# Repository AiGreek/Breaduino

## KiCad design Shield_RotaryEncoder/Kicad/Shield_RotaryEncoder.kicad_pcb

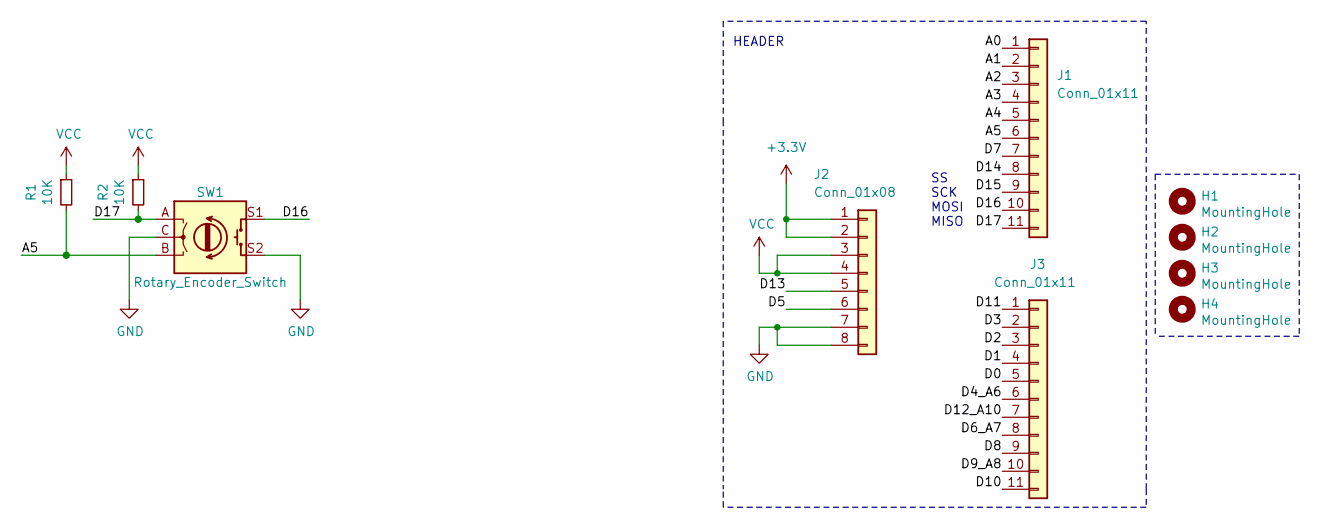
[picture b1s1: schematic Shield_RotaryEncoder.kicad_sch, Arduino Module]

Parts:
H1, H2, H3, H4: MountingHole; MountingHole_2.2mm_M2_Pad
J1, J3: Conn_01x11; PinHeader_1x11_P2.54mm_Vertical
J2: Conn_01x08; PinHeader_1x08_P2.54mm_Vertical
R1, R2: 10K; R_0603_1608Metric_Pad0.98x0.95mm_HandSolder
SW1: Rotary_Encoder_Switch; RotaryEncoder_Alps_EC11E-Switch_Vertical_H20mm

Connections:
+3V3: J2.1, J2.2
/A0: J1.1
/A1: J1.2
/A2: J1.3
/A3: J1.4
/A4: J1.5
/A5: J1.6, R1.2, SW1.B
/D0: J3.5
/D1: J3.4
/D2: J3.3
/D3: J3.2
/D4_A6: J3.6
/D5: J2.6
/D6_A7: J3.8
/D7: J1.7
/D8: J3.9
/D9_A8: J3.10
/D10: J3.11
/D11: J3.1
/D12_A10: J3.7
/D13: J2.5
/D14: J1.8
/D15: J1.9
/D16: J1.10, SW1.S1
/D17: J1.11, R2.2, SW1.A
GND: J2.7, J2.8, SW1.C, SW1.S2
VCC: J2.3, J2.4, R1.1, R2.1

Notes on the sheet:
HEADER
SS SCK MOSI MISO

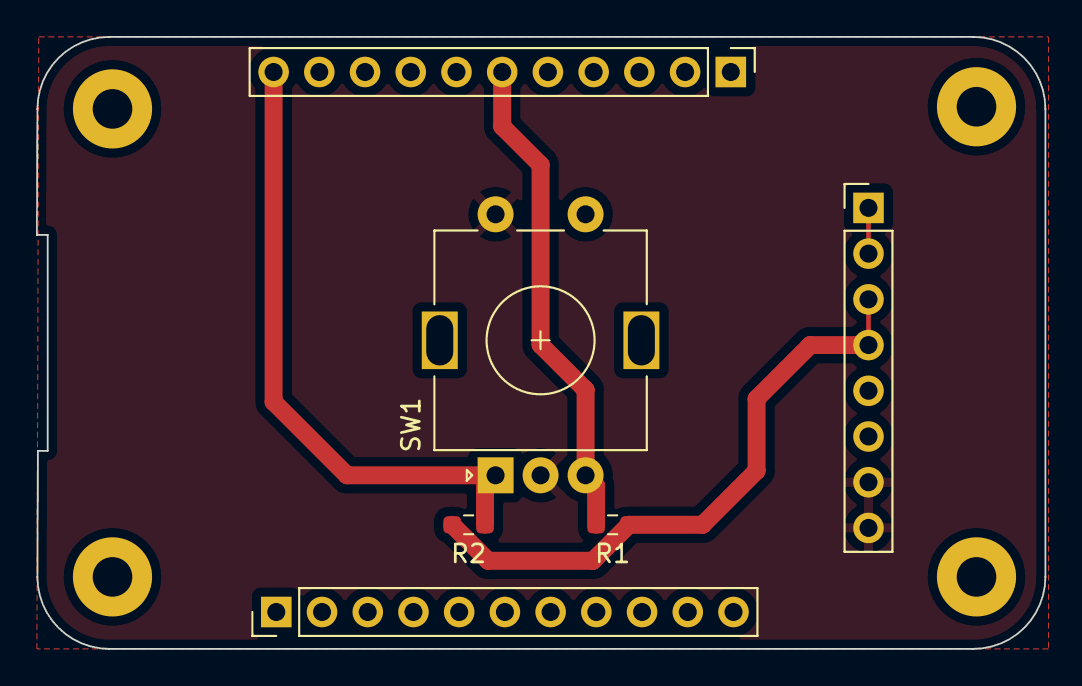
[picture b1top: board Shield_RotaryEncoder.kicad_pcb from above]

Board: 2 copper layers, 56.0 x 34.0 mm, 10 parts (0 on the bottom side), 6 nets.

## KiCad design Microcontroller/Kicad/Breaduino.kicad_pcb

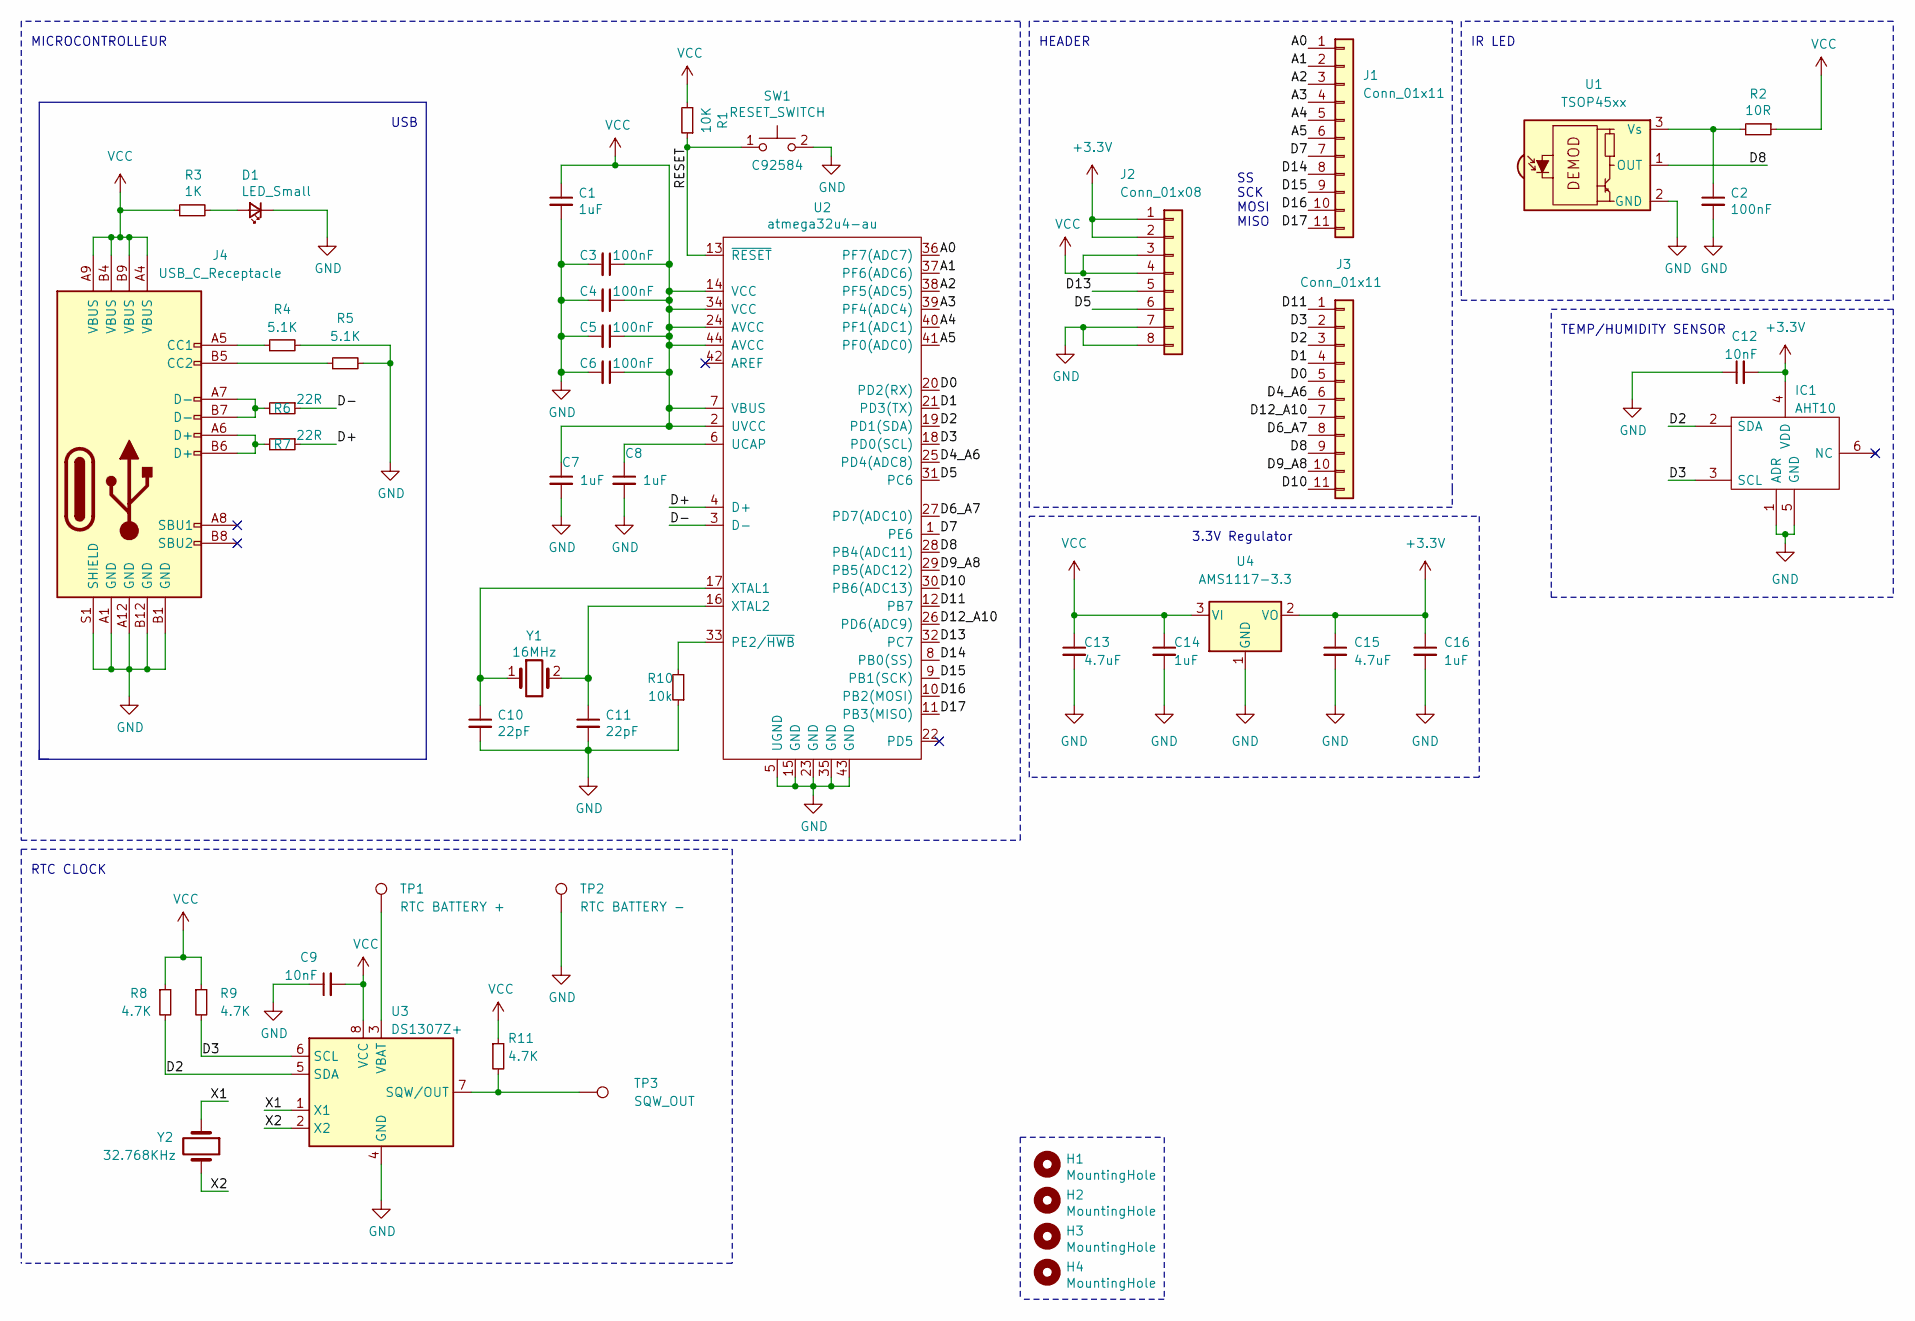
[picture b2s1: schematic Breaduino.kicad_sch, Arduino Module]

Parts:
C1, C7, C8, C14, C16: 1uF; C_0603_1608Metric_Pad1.08x0.95mm_HandSolder; LCSC C15849
C2, C3, C4, C5, C6: 100nF; C_0603_1608Metric_Pad1.08x0.95mm_HandSolder; LCSC C83054
C9, C12: 10nF; C_0603_1608Metric_Pad1.08x0.95mm_HandSolder; LCSC C15849
C10, C11: 22pF; C_0603_1608Metric_Pad1.08x0.95mm_HandSolder; LCSC C1653
C13, C15: 4.7uF; C_0603_1608Metric_Pad1.08x0.95mm_HandSolder; LCSC C19666
D1: LED_Small; LED_0603_1608Metric_Pad1.05x0.95mm_HandSolder; LCSC C72044
H1, H2, H3, H4: MountingHole; MountingHole_2.2mm_M2_Pad
IC1: AHT10; LCSC C368909
J1, J3: Conn_01x11; PinHeader_1x11_P2.54mm_Vertical
J2: Conn_01x08; PinHeader_1x08_P2.54mm_Vertical
J4: USB_C_Receptacle; USB_C_Receptacle_JAE_DX07S016JA1R1500; LCSC C668624
R1: 10K; R_0603_1608Metric_Pad0.98x0.95mm_HandSolder; LCSC C25804
R2: 10R; R_0603_1608Metric_Pad0.98x0.95mm_HandSolder; LCSC C25804
R3: 1K; R_0603_1608Metric_Pad0.98x0.95mm_HandSolder; LCSC C21190
R4, R5: 5.1K; R_0603_1608Metric_Pad0.98x0.95mm_HandSolder; LCSC C26000
R6, R7: 22R; R_0603_1608Metric_Pad0.98x0.95mm_HandSolder; LCSC C23345
R8, R9, R11: 4.7K; R_0603_1608Metric_Pad0.98x0.95mm_HandSolder; LCSC C23162
R10: 10k; R_0603_1608Metric_Pad0.98x0.95mm_HandSolder; LCSC C25804
SW1: RESET_SWITCH; SW_SPST_SKQG_WithStem; LCSC C92584
TP1: RTC BATTERY +; TestPoint_Keystone_5015_Micro-Minature
TP2: RTC BATTERY -; TestPoint_Keystone_5015_Micro-Minature
TP3: SQW_OUT; TestPoint_Keystone_5015_Micro-Minature
U1: TSOP45xx; Vishay_MOLD-3Pin; LCSC C124647
U2: atmega32u4-au; TQFP-44_10x10mm_P0.8mm; LCSC C44854
U3: DS1307Z+; SOIC-8_3.9x4.9mm_P1.27mm; LCSC C9868
U4: AMS1117-3.3; SOT-223-3_TabPin2; LCSC C6186
Y1: 16MHz; Crystal_SMD_3225-4Pin_3.2x2.5mm; LCSC C16171
Y2: 32.768KHz; DST210AC32768KHz; LCSC C99009

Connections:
+3V3: C12.2, C15.1, C16.1, IC1.4 (VDD), J2.1, J2.2, U4.2 (VO)
/A0: J1.1, U2.36 (PF7(ADC7))
/A1: J1.2, U2.37 (PF6(ADC6))
/A2: J1.3, U2.38 (PF5(ADC5))
/A3: J1.4, U2.39 (PF4(ADC4))
/A4: J1.5, U2.40 (PF1(ADC1))
/A5: J1.6, U2.41 (PF0(ADC0))
/D0: J3.5, U2.20 (PD2(RX))
/D1: J3.4, U2.21 (PD3(TX))
/D2: IC1.2 (SDA), J3.3, R8.2, U2.19 (PD1(SDA)), U3.5 (SDA)
/D3: IC1.3 (SCL), J3.2, R9.2, U2.18 (PD0(SCL)), U3.6 (SCL)
/D4_A6: J3.6, U2.25 (PD4(ADC8))
/D5: J2.6, U2.31 (PC6)
/D6_A7: J3.8, U2.27 (PD7(ADC10))
/D7: J1.7, U2.1 (PE6)
/D8: J3.9, U1.1 (OUT), U2.28 (PB4(ADC11))
/D9_A8: J3.10, U2.29 (PB5(ADC12))
/D10: J3.11, U2.30 (PB6(ADC13))
/D11: J3.1, U2.12 (PB7)
/D12_A10: J3.7, U2.26 (PD6(ADC9))
/D13: J2.5, U2.32 (PC7)
/D14: J1.8, U2.8 (PB0(SS))
/D15: J1.9, U2.9 (PB1(SCK))
/D16: J1.10, U2.10 (PB2(MOSI))
/D17: J1.11, U2.11 (PB3(MISO))
/D+: R7.1, U2.4 (D+)
/D-: R6.1, U2.3 (D-)
/RESET: R1.1, SW1.1, U2.13 (~RESET)
/X1: U3.1 (X1), Y2.1
/X2: U3.2 (X2), Y2.2
GND: C1.2, C2.2, C3.2, C4.2, C5.2, C6.2, C7.2, C8.2, C9.1, C10.2, C11.2, C12.1, C13.2, C14.2, C15.2, C16.2, D1.1 (K), IC1.1 (ADR), IC1.5 (GND), J2.7, J2.8, J4.A1 (GND), J4.A12 (GND), J4.B1 (GND), J4.B12 (GND), J4.S1 (SHIELD), R4.2, R5.2, R10.1, SW1.2, TP2.1, U1.2 (GND), U2.5 (UGND), U2.15 (GND), U2.23 (GND), U2.35 (GND), U2.43 (GND), U3.4 (GND), U4.1 (GND)
unnamed: D1.2 (A), R3.2
unnamed: J4.A5 (CC1), R4.1
unnamed: J4.B5 (CC2), R5.1
unnamed: J4.A6 (D+), J4.B6 (D+), R7.2
unnamed: J4.A7 (D-), J4.B7 (D-), R6.2
unnamed: C2.1, R2.2, U1.3 (Vs)
unnamed: R10.2, U2.33 (PE2/~HWB)
unnamed: C8.1, U2.6 (UCAP)
unnamed: C10.1, U2.17 (XTAL1), Y1.1
unnamed: C11.1, U2.16 (XTAL2), Y1.2
unnamed: R11.2, TP3.1, U3.7 (SQW/OUT)
unnamed: TP1.1, U3.3 (VBAT)
VCC: C1.1, C3.1, C4.1, C5.1, C6.1, C7.1, C9.2, C13.1, C14.1, J2.3, J2.4, J4.A4 (VBUS), J4.A9 (VBUS), J4.B4 (VBUS), J4.B9 (VBUS), R1.2, R2.1, R3.1, R8.1, R9.1, R11.1, U2.2 (UVCC), U2.7 (VBUS), U2.14 (VCC), U2.24 (AVCC), U2.34 (VCC), U2.44 (AVCC), U3.8 (VCC), U4.3 (VI)

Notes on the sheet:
HEADER
TEMP/HUMIDITY SENSOR
MICROCONTROLLEUR
IR LED
RTC CLOCK
SS SCK MOSI MISO
USB
3.3V Regulator

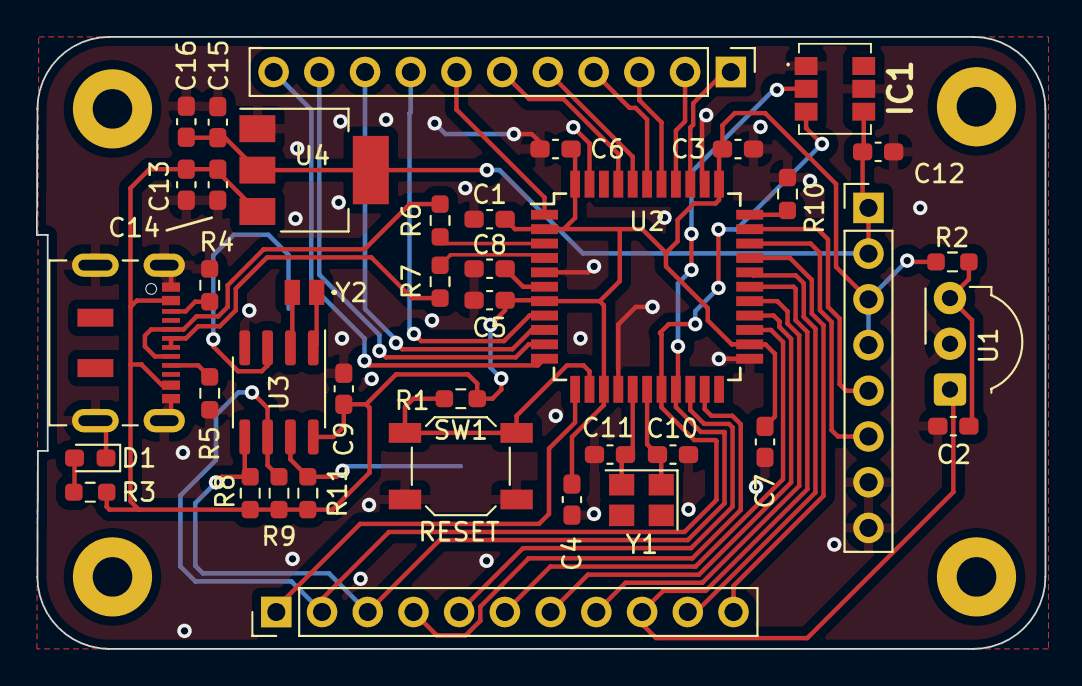
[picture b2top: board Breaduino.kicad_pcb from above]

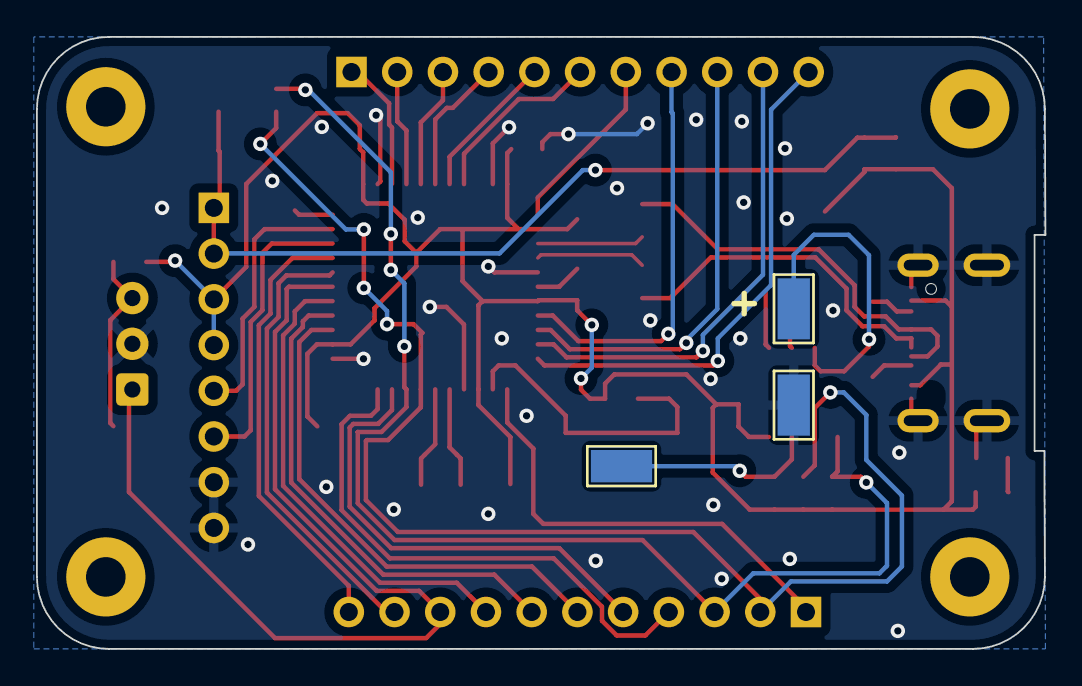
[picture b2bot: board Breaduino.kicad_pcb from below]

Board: 2 copper layers, 56.0 x 34.0 mm, 47 parts (3 on the bottom side), 44 nets.

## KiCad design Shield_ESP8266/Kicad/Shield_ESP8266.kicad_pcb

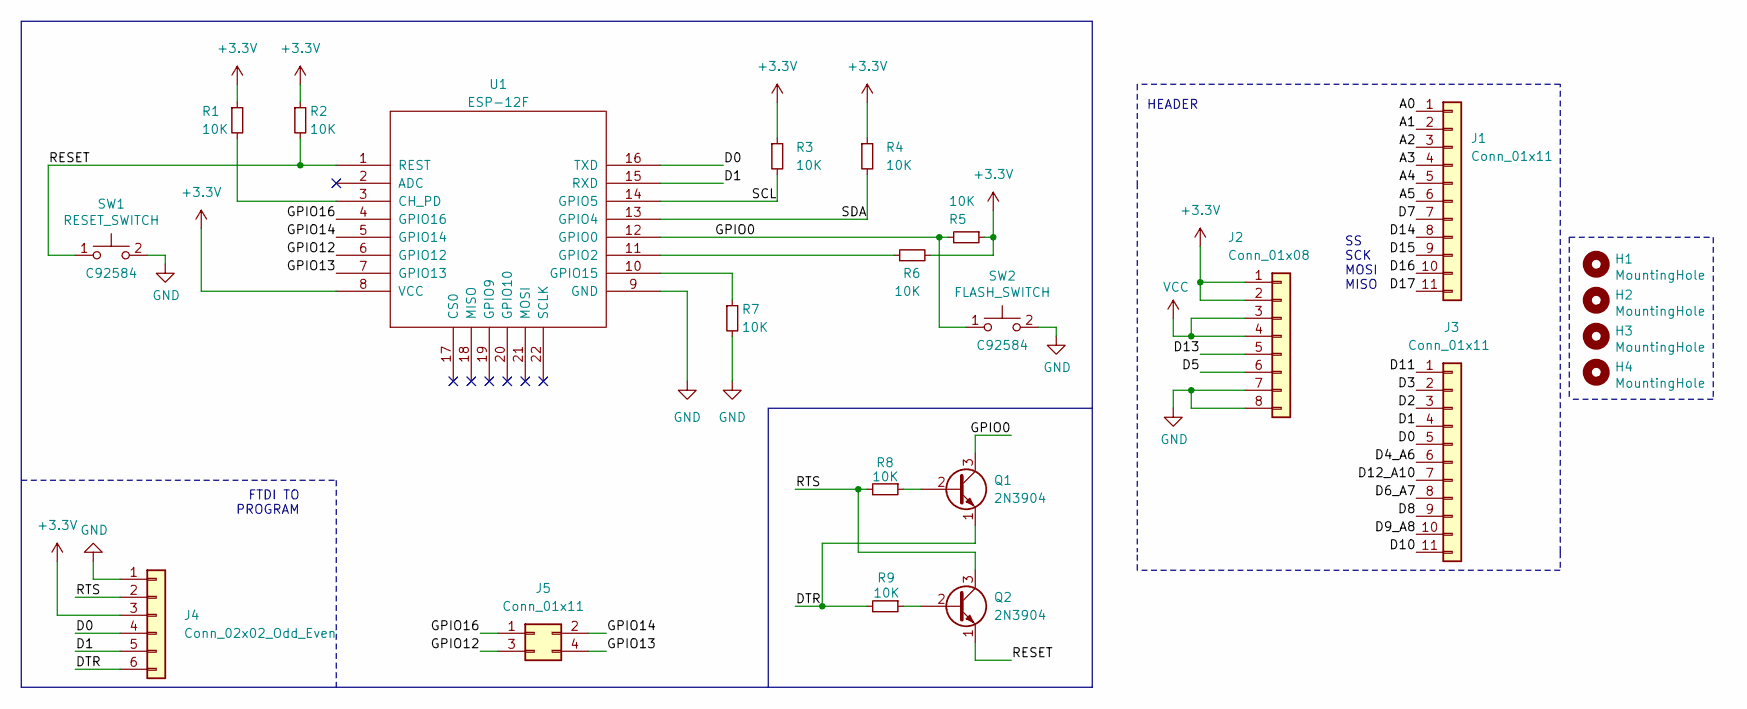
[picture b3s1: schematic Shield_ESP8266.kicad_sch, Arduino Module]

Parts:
H1, H2, H3, H4: MountingHole; MountingHole_2.2mm_M2_Pad
J1, J3: Conn_01x11; PinHeader_1x11_P2.54mm_Vertical
J2: Conn_01x08; PinHeader_1x08_P2.54mm_Vertical
J4: Conn_02x02_Odd_Even; PinHeader_1x06_P2.54mm_Vertical
J5: Conn_01x11; PinSocket_2x02_P2.54mm_Vertical
Q1, Q2: 2N3904; SOT-23
R1, R2, R5, R6, R7, R8, R9: 10K; R_0603_1608Metric_Pad0.98x0.95mm_HandSolder; LCSC C25804
R3, R4: 10K; R_0603_1608Metric_Pad0.98x0.95mm_HandSolder
SW1: RESET_SWITCH; SW_SPST_SKQG_WithStem; LCSC C92584
SW2: FLASH_SWITCH; SW_SPST_SKQG_WithStem; LCSC C92584
U1: ESP-12F; ESP-12E_SMD

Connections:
+3V3: J2.1, J2.2, J4.3, R1.1, R2.1, R3.1, R4.1, R5.1, R6.2, U1.8 (VCC)
/A0: J1.1
/A1: J1.2
/A2: J1.3
/A3: J1.4
/A4: J1.5
/A5: J1.6
/D0: J3.5, J4.4, U1.16 (TXD)
/D1: J3.4, J4.5, U1.15 (RXD)
/D2: J3.3
/D3: J3.2
/D4_A6: J3.6
/D5: J2.6
/D6_A7: J3.8
/D7: J1.7
/D8: J3.9
/D9_A8: J3.10
/D10: J3.11
/D11: J3.1
/D12_A10: J3.7
/D13: J2.5
/D14: J1.8
/D15: J1.9
/D16: J1.10
/D17: J1.11
/DTR: J4.6, Q1.1 (E), R9.2
/GPIO0: Q1.3 (C), R5.2, SW2.1, U1.12 (GPIO0)
/GPIO12: J5.3, U1.6 (GPIO12)
/GPIO13: J5.4, U1.7 (GPIO13)
/GPIO14: J5.2, U1.5 (GPIO14)
/GPIO16: J5.1, U1.4 (GPIO16)
/RESET: Q2.1 (E), R2.2, SW1.1, U1.1 (REST)
/RTS: J4.2, Q2.3 (C), R8.2
/SCL: R3.2, U1.14 (GPIO5)
/SDA: R4.2, U1.13 (GPIO4)
GND: J2.7, J2.8, J4.1, R7.2, SW1.2, SW2.2, U1.9 (GND)
unnamed: Q1.2 (B), R8.1
unnamed: Q2.2 (B), R9.1
unnamed: R1.2, U1.3 (CH_PD)
unnamed: R6.1, U1.11 (GPIO2)
unnamed: R7.1, U1.10 (GPIO15)
VCC: J2.3, J2.4

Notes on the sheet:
HEADER
FTDI TO PROGRAM
SS SCK MOSI MISO

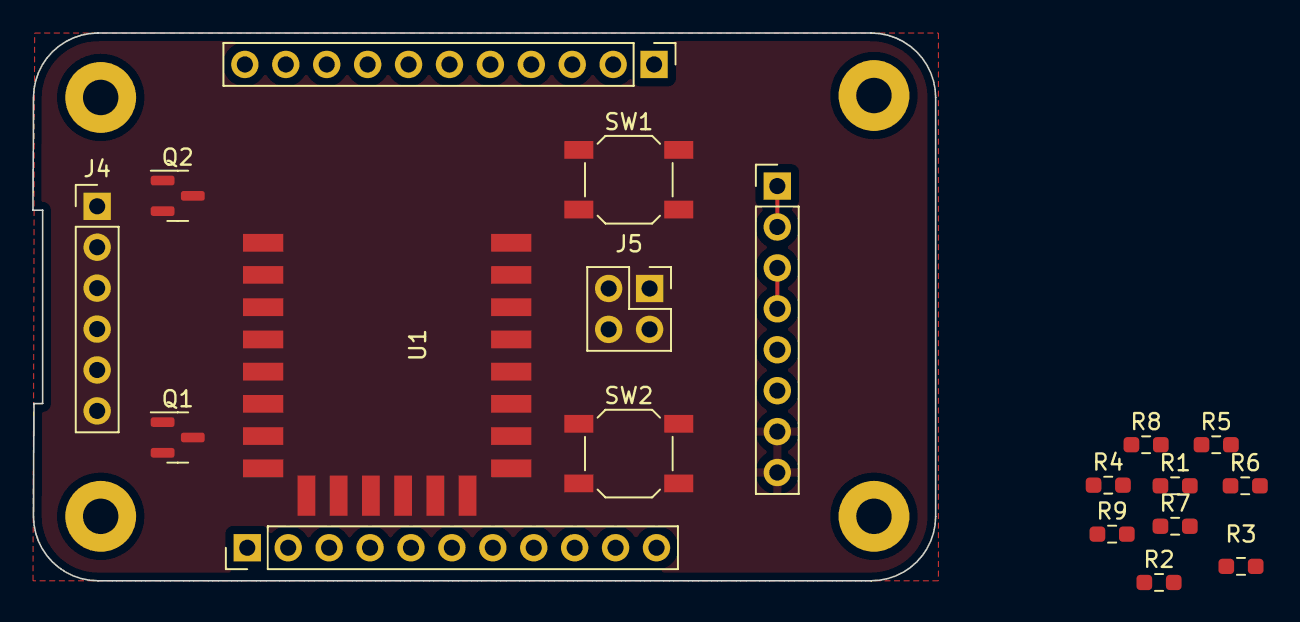
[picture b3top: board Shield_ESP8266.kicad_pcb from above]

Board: 2 copper layers, 56.0 x 34.0 mm, 23 parts (0 on the bottom side), 20 nets.
